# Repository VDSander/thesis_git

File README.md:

# thesis_git
All files concerning master's thesis

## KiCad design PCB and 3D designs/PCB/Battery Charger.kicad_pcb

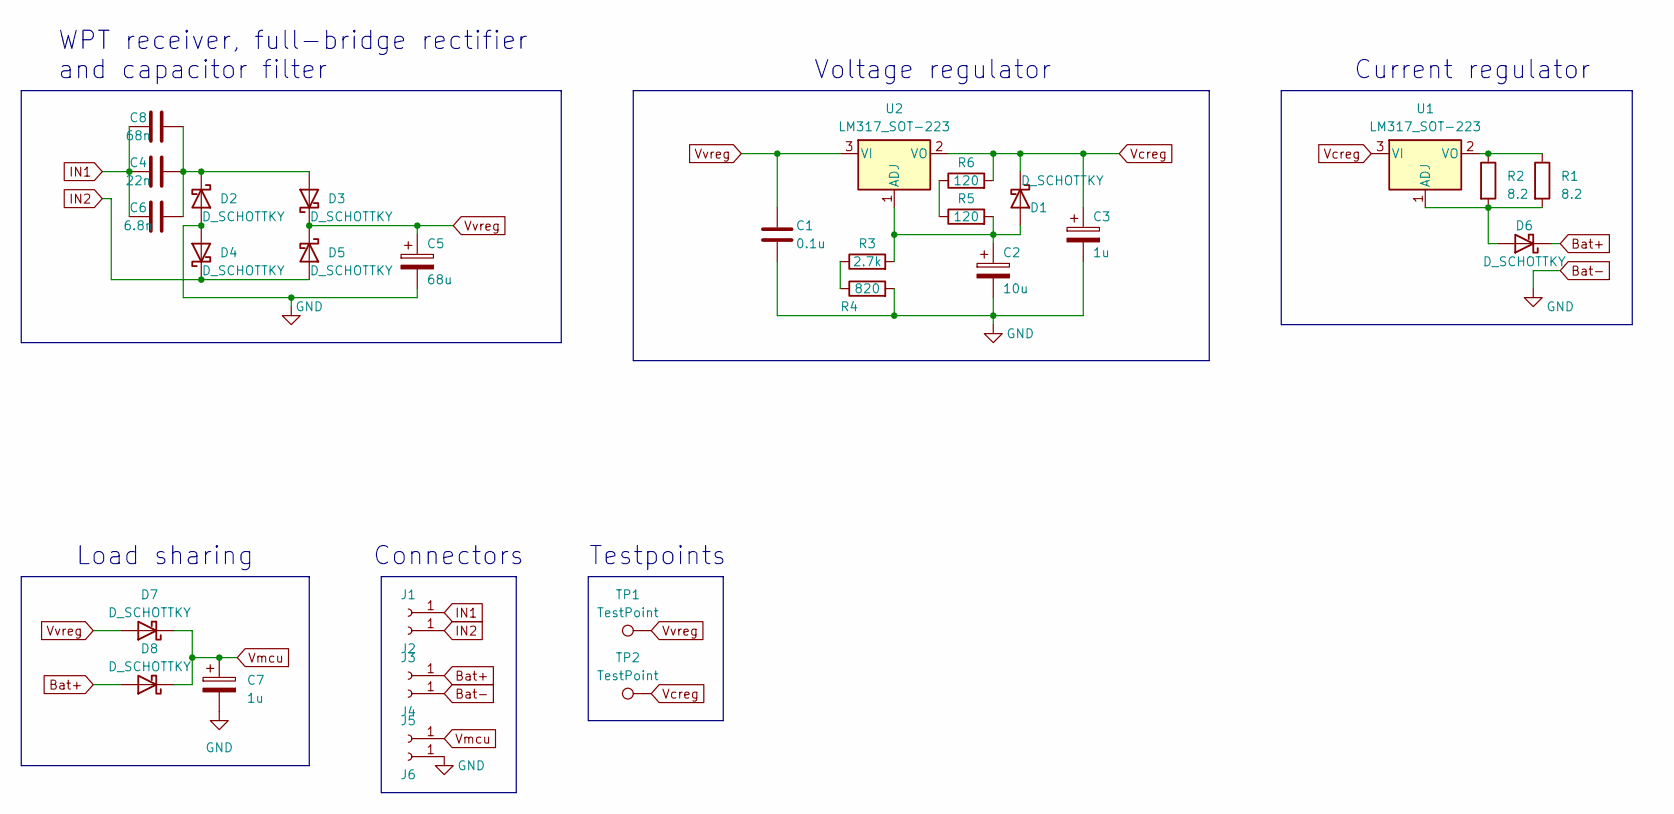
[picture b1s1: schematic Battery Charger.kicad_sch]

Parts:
C1: 0.1u; C_0805_2012Metric_Pad1.18x1.45mm_HandSolder
C2: 10u; CP_Radial_D13.0mm_P5.00mm
C3, C7: 1u; CP_Elec_4x5.4
C4: 22n; C_0805_2012Metric_Pad1.18x1.45mm_HandSolder
C5: 68u; CP_Radial_D13.0mm_P5.00mm
C6: 6.8n; C_0805_2012Metric_Pad1.18x1.45mm_HandSolder
C8: 68n; C_0805_2012Metric_Pad1.18x1.45mm_HandSolder
D1, D2, D3, D4, D5, D6, D7, D8: D_SCHOTTKY; D_SOD-128
J1: COIL1; SolderWirePad_1x01_SMD_1x2mm
J2: COIL2; SolderWirePad_1x01_SMD_1x2mm
J3: +BAT; SolderWirePad_1x01_SMD_1x2mm
J4: -BAT; SolderWirePad_1x01_SMD_1x2mm
J5: VMCU; SolderWirePad_1x01_SMD_1x2mm
J6: GNDMCU; SolderWirePad_1x01_SMD_1x2mm
R1, R2: 8.2; R_0805_2012Metric_Pad1.20x1.40mm_HandSolder
R3: 2.7k; R_0805_2012Metric_Pad1.20x1.40mm_HandSolder
R4: 820; R_0805_2012Metric_Pad1.20x1.40mm_HandSolder
R5, R6: 120; R_0805_2012Metric_Pad1.20x1.40mm_HandSolder
TP1, TP2: TestPoint; TestPoint_Pad_D1.0mm
U1, U2: LM317_SOT-223; TO-220-3_Vertical

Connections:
Bat+: D6.1 (K), D8.2 (A), J3.1
Bat-: C1.2, C2.2, C3.2, C5.2, C7.2, D2.2 (A), D4.2 (A), J4.1, J6.1, R4.2
IN1: C4.1, C6.1, C8.1, J1.1
IN2: D4.1 (K), D5.2 (A), J2.1
unnamed: C2.1, D1.2 (A), R3.2, R5.2, U2.1 (ADJ)
unnamed: C4.2, C6.2, C8.2, D2.1 (K), D3.2 (A)
unnamed: D6.2 (A), R1.2, R2.2, U1.1 (ADJ)
unnamed: R3.1, R4.1
unnamed: R5.1, R6.1
unnamed: R1.1, R2.1, U1.2 (VO)
Vcreg: C3.1, D1.1 (K), R6.2, TP2.1, U1.3 (VI), U2.2 (VO)
Vmcu: C7.1, D7.1 (K), D8.1 (K), J5.1
Vvreg: C1.1, C5.1, D3.1 (K), D5.1 (K), D7.2 (A), TP1.1, U2.3 (VI)

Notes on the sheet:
Current regulator
Load sharing
Connectors
Testpoints
WPT receiver, full-bridge rectifier and capacitor filter
Voltage regulator

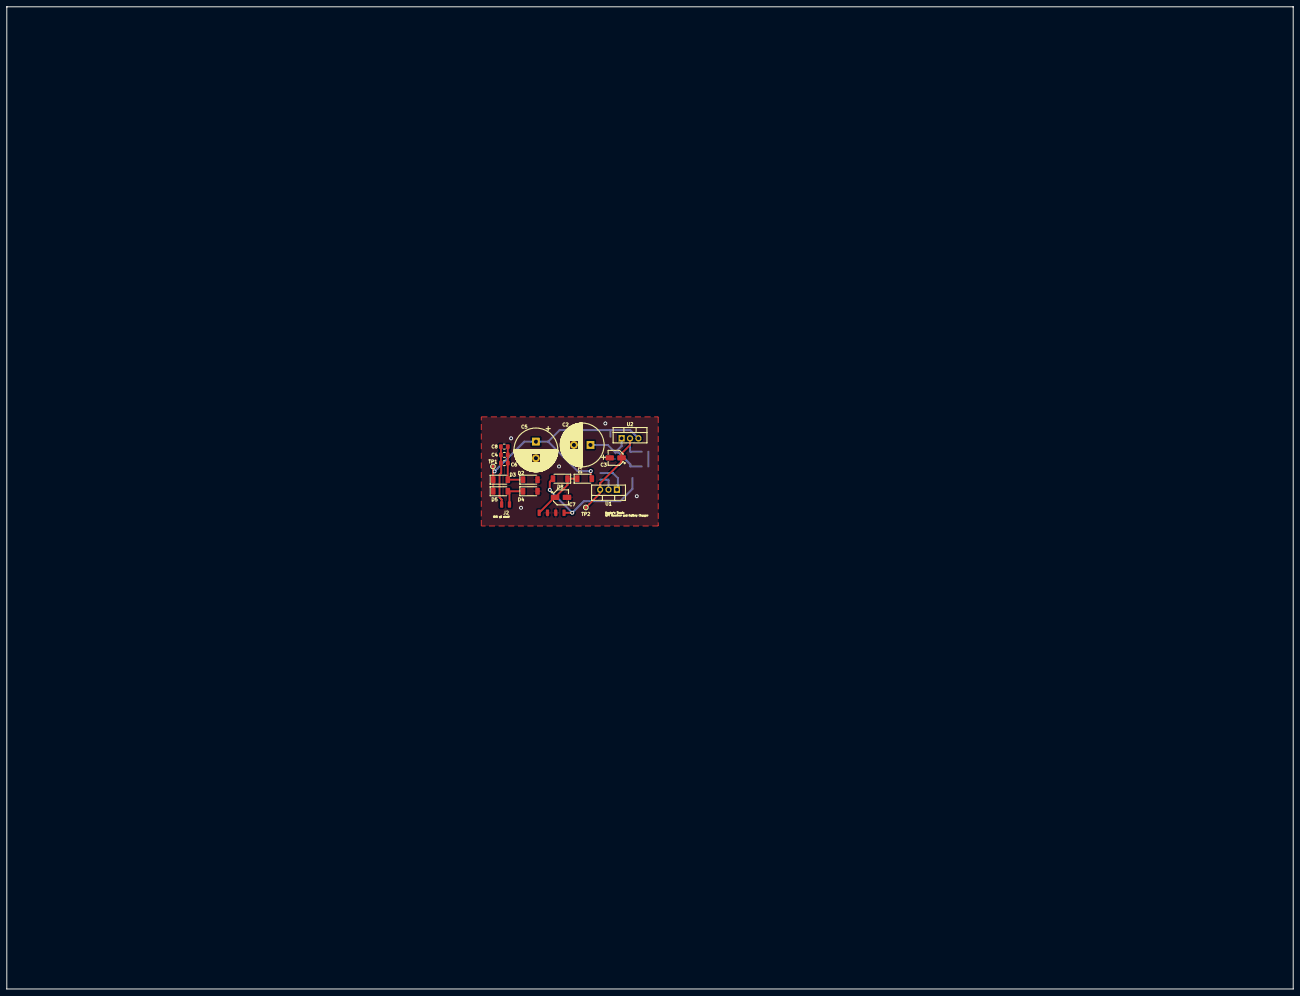
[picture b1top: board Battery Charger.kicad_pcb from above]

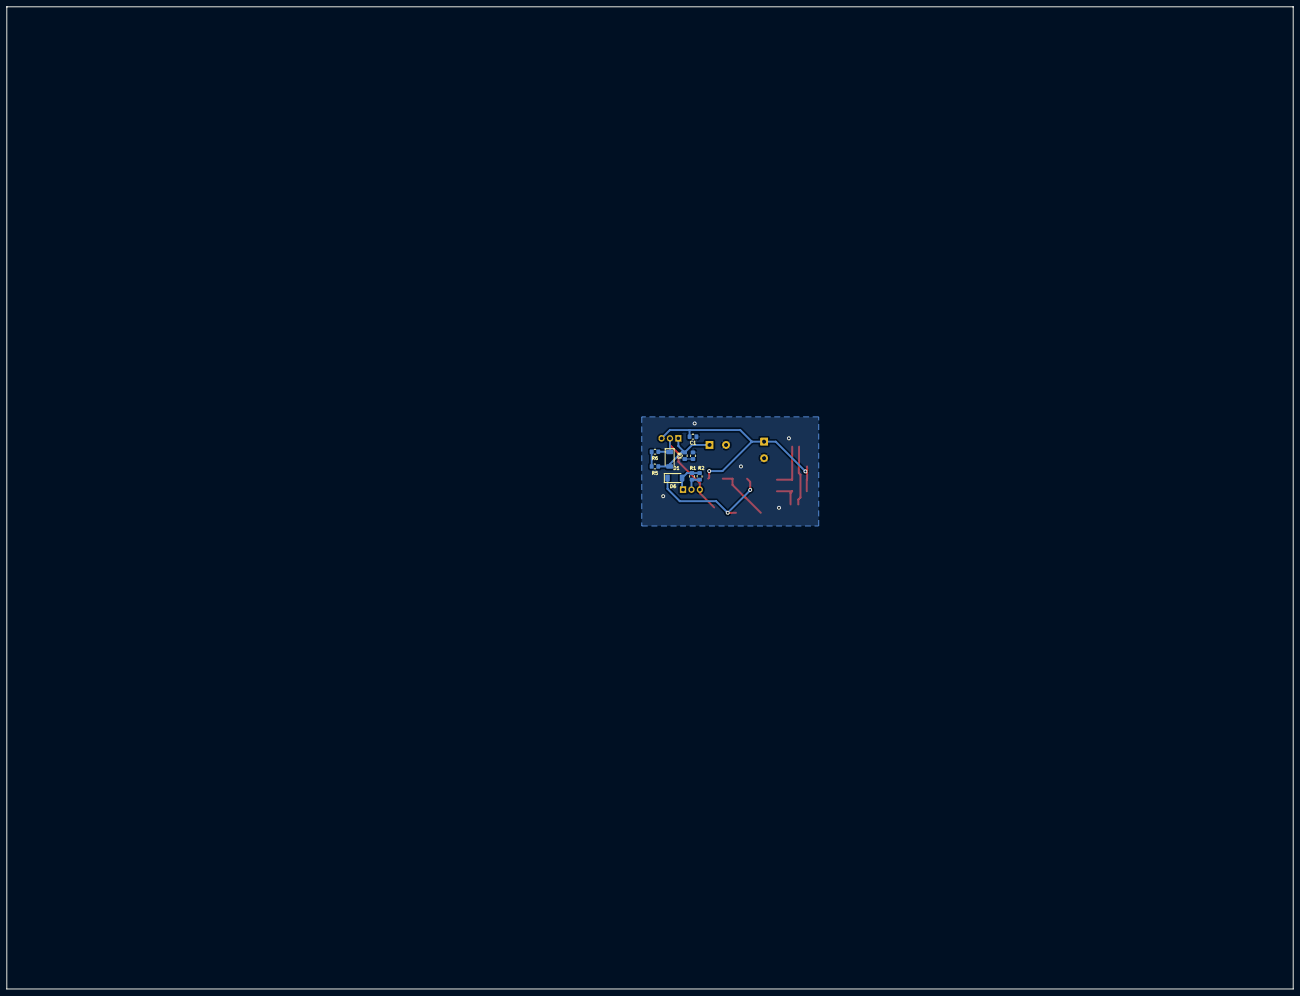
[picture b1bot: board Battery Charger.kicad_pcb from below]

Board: 2 copper layers, 389.0 x 297.0 mm, 32 parts (9 on the bottom side), 13 nets.
